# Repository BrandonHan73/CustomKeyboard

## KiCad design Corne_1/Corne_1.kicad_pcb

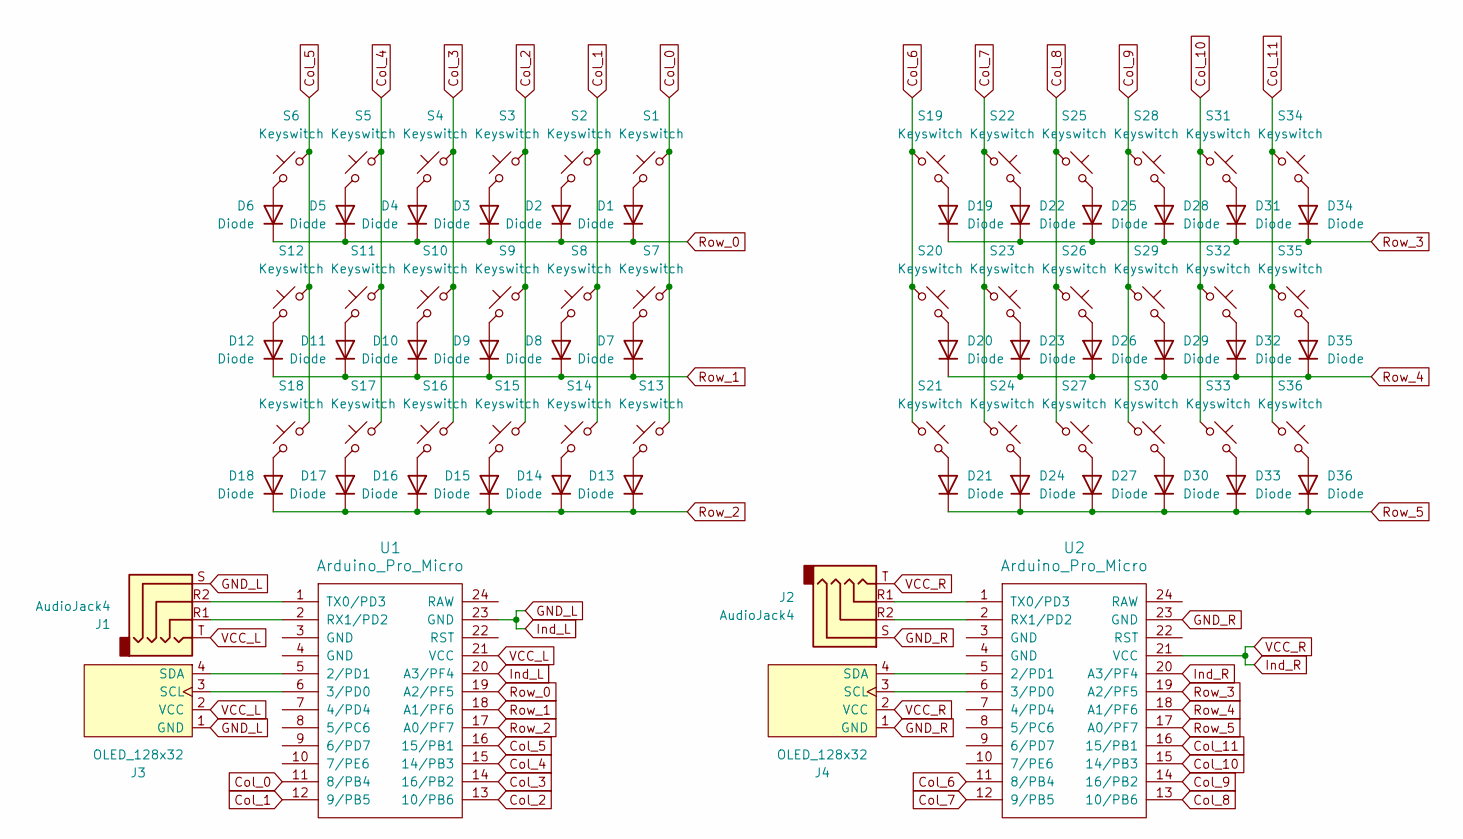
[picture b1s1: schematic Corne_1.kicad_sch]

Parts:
D1, D2, D3, D4, D5, D6, D7, D8, D9, D10, D11, D12, D13, D14, D15, D16, D17, D18, D19, D20, D21, D22, D23, D24, D25, D26, D27, D28, D29, D30, D31, D32, D33, D34, D35, D36: Diode; Diode_DO-35
J1, J2: AudioJack4; Jack_3.5mm_PJ320D_Horizontal
J3, J4: OLED_128x32
S1, S19: Keyswitch; Hotswap_Choc_V1_1.50u
S2, S3, S4, S5, S6, S7, S8, S9, S10, S11, S12, S13, S14, S15, S16, S17, S18, S20, S21, S22, S23, S24, S25, S26, S27, S28, S29, S30, S31, S32, S33, S34, S35, S36: Keyswitch; Hotswap_Choc_V1_1.00u
U1, U2: Arduino_Pro_Micro

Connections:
Col_0: S1.1, S7.1, S13.1, U1.11 (8/PB4)
Col_1: S2.1, S8.1, S14.1, U1.12 (9/PB5)
Col_2: S3.1, S9.1, S15.1, U1.13 (10/PB6)
Col_3: S4.1, S10.1, S16.1, U1.14 (16/PB2)
Col_4: S5.1, S11.1, S17.1, U1.15 (14/PB3)
Col_5: S6.1, S12.1, S18.1, U1.16 (15/PB1)
Col_6: S19.1, S20.1, S21.1, U2.11 (8/PB4)
Col_7: S22.1, S23.1, S24.1, U2.12 (9/PB5)
Col_8: S25.1, S26.1, S27.1, U2.13 (10/PB6)
Col_9: S28.1, S29.1, S30.1, U2.14 (16/PB2)
Col_10: S31.1, S32.1, S33.1, U2.15 (14/PB3)
Col_11: S34.1, S35.1, S36.1, U2.16 (15/PB1)
GND_L: J1.S, J3.1 (GND), U1.20 (A3/PF4), U1.23 (GND)
GND_R: J2.S, J4.1 (GND), U2.23 (GND)
Ind_R: J2.T, J4.2 (VCC), U2.20 (A3/PF4), U2.21 (VCC)
unnamed: D1.2 (A), S1.2
unnamed: D2.2 (A), S2.2
unnamed: D3.2 (A), S3.2
unnamed: D4.2 (A), S4.2
unnamed: D5.2 (A), S5.2
unnamed: D6.2 (A), S6.2
unnamed: D7.2 (A), S7.2
unnamed: D8.2 (A), S8.2
unnamed: D9.2 (A), S9.2
unnamed: D10.2 (A), S10.2
unnamed: D11.2 (A), S11.2
unnamed: D12.2 (A), S12.2
unnamed: D13.2 (A), S13.2
unnamed: D14.2 (A), S14.2
unnamed: D15.2 (A), S15.2
unnamed: D16.2 (A), S16.2
unnamed: D17.2 (A), S17.2
unnamed: D18.2 (A), S18.2
unnamed: D19.2 (A), S19.2
unnamed: D20.2 (A), S20.2
unnamed: D21.2 (A), S21.2
unnamed: D22.2 (A), S22.2
unnamed: D23.2 (A), S23.2
unnamed: D24.2 (A), S24.2
unnamed: D25.2 (A), S25.2
unnamed: D26.2 (A), S26.2
unnamed: D27.2 (A), S27.2
unnamed: D28.2 (A), S28.2
unnamed: D29.2 (A), S29.2
unnamed: D30.2 (A), S30.2
unnamed: D31.2 (A), S31.2
unnamed: D32.2 (A), S32.2
unnamed: D33.2 (A), S33.2
unnamed: D34.2 (A), S34.2
unnamed: D35.2 (A), S35.2
unnamed: D36.2 (A), S36.2
unnamed: J3.3 (SCL), U1.6 (3/PD0)
unnamed: J3.4 (SDA), U1.5 (2/PD1)
unnamed: J4.3 (SCL), U2.6 (3/PD0)
unnamed: J4.4 (SDA), U2.5 (2/PD1)
unnamed: J1.R1, U1.2 (RX1/PD2)
unnamed: J1.R2, U1.1 (TX0/PD3)
unnamed: J2.R2, U2.2 (RX1/PD2)
unnamed: J2.R1, U2.1 (TX0/PD3)
Row_0: D1.1 (K), D2.1 (K), D3.1 (K), D4.1 (K), D5.1 (K), D6.1 (K), U1.19 (A2/PF5)
Row_1: D7.1 (K), D8.1 (K), D9.1 (K), D10.1 (K), D11.1 (K), D12.1 (K), U1.18 (A1/PF6)
Row_2: D13.1 (K), D14.1 (K), D15.1 (K), D16.1 (K), D17.1 (K), D18.1 (K), U1.17 (A0/PF7)
Row_3: D19.1 (K), D22.1 (K), D25.1 (K), D28.1 (K), D31.1 (K), D34.1 (K), U2.19 (A2/PF5)
Row_4: D20.1 (K), D23.1 (K), D26.1 (K), D29.1 (K), D32.1 (K), D35.1 (K), U2.18 (A1/PF6)
Row_5: D21.1 (K), D24.1 (K), D27.1 (K), D30.1 (K), D33.1 (K), D36.1 (K), U2.17 (A0/PF7)
VCC_L: J1.T, J3.2 (VCC), U1.21 (VCC)

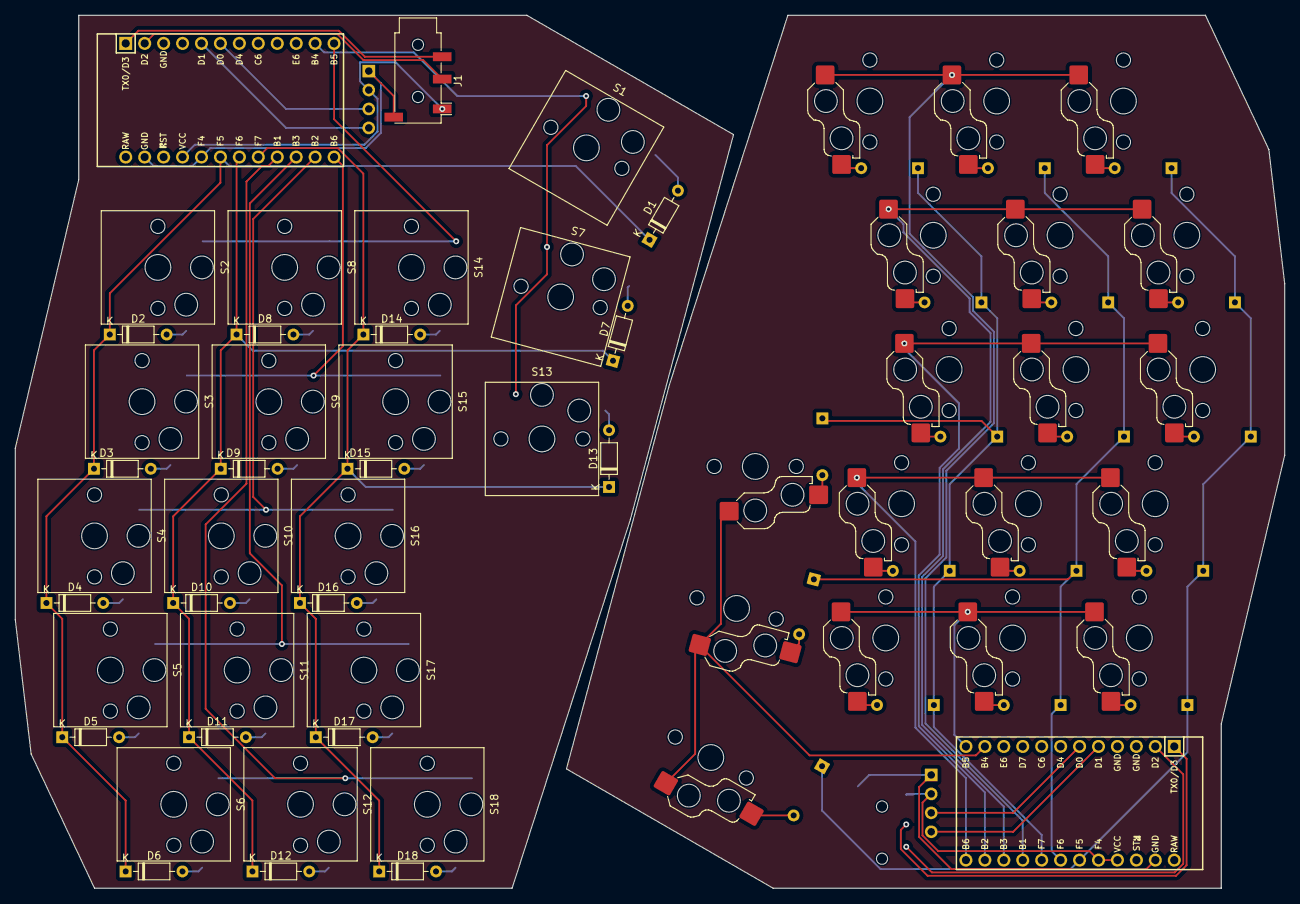
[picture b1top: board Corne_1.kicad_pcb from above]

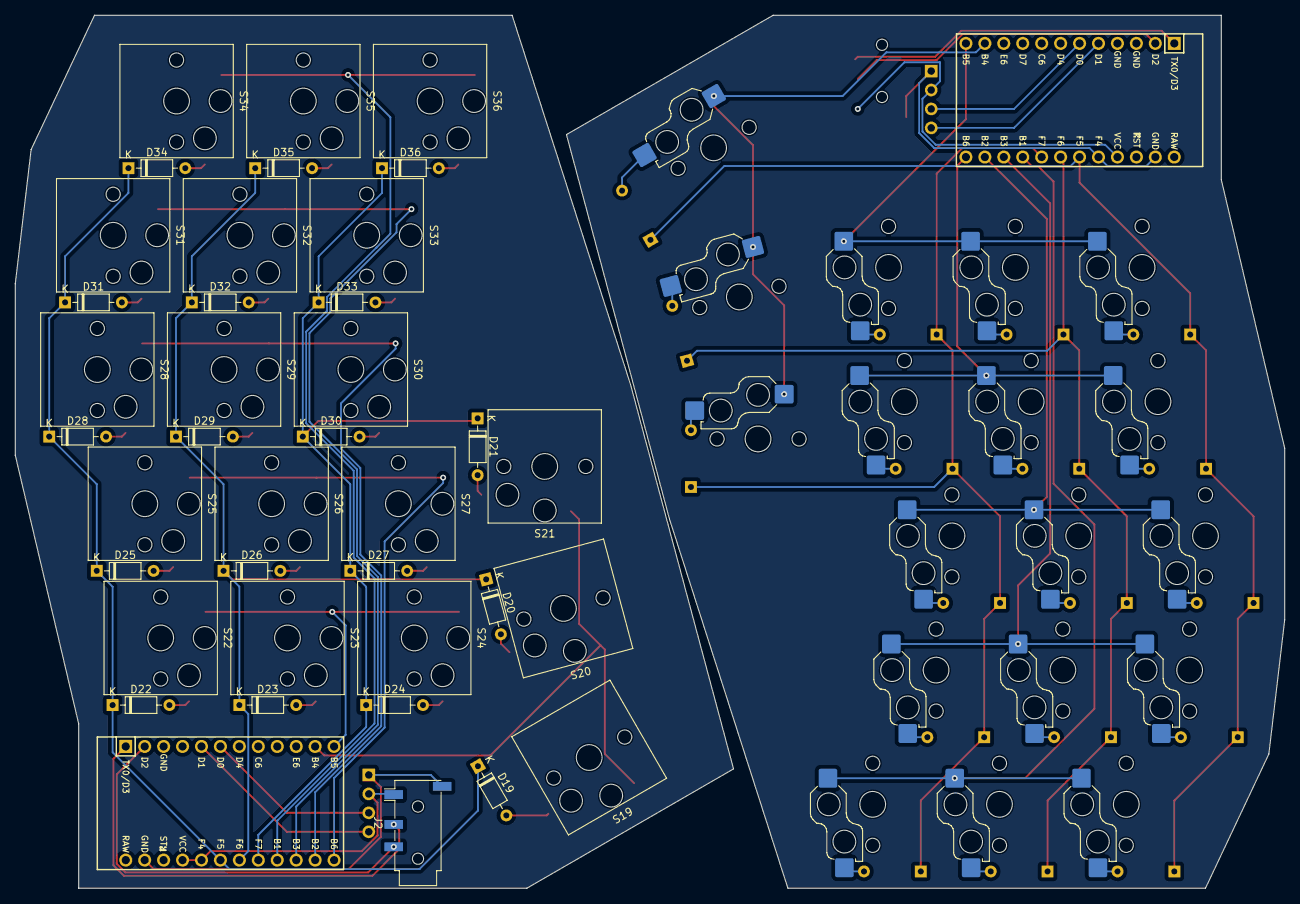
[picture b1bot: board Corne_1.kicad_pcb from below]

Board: 2 copper layers, 170.2 x 117.1 mm, 78 parts (39 on the bottom side), 66 nets.

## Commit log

2024-07-22 Upload code
2024-07-22 Added ino file
2024-07-30 Added KiCad files to repo
